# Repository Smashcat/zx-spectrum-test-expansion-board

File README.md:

# zx-spectrum-test-expansion-board

## A test board to plug into the ZX Spectrum expansion port for dev use

This board is used to break out the signals from the expansion header for development use. All signals, except for power, are converted to 3.3V for use with modern microcontrollers. The buttons for WAIT and RESET are optional, but handy for development.

The production folder contains files to submit the board for PCBA production at [JLCPCB](https://jlcpcb.com/) (only the SMD components - as adding thru-hole parts adds 1-2 days to production and costs quite a bit extra - and let's face it, it's pretty simple to solder the headers and buttons!)

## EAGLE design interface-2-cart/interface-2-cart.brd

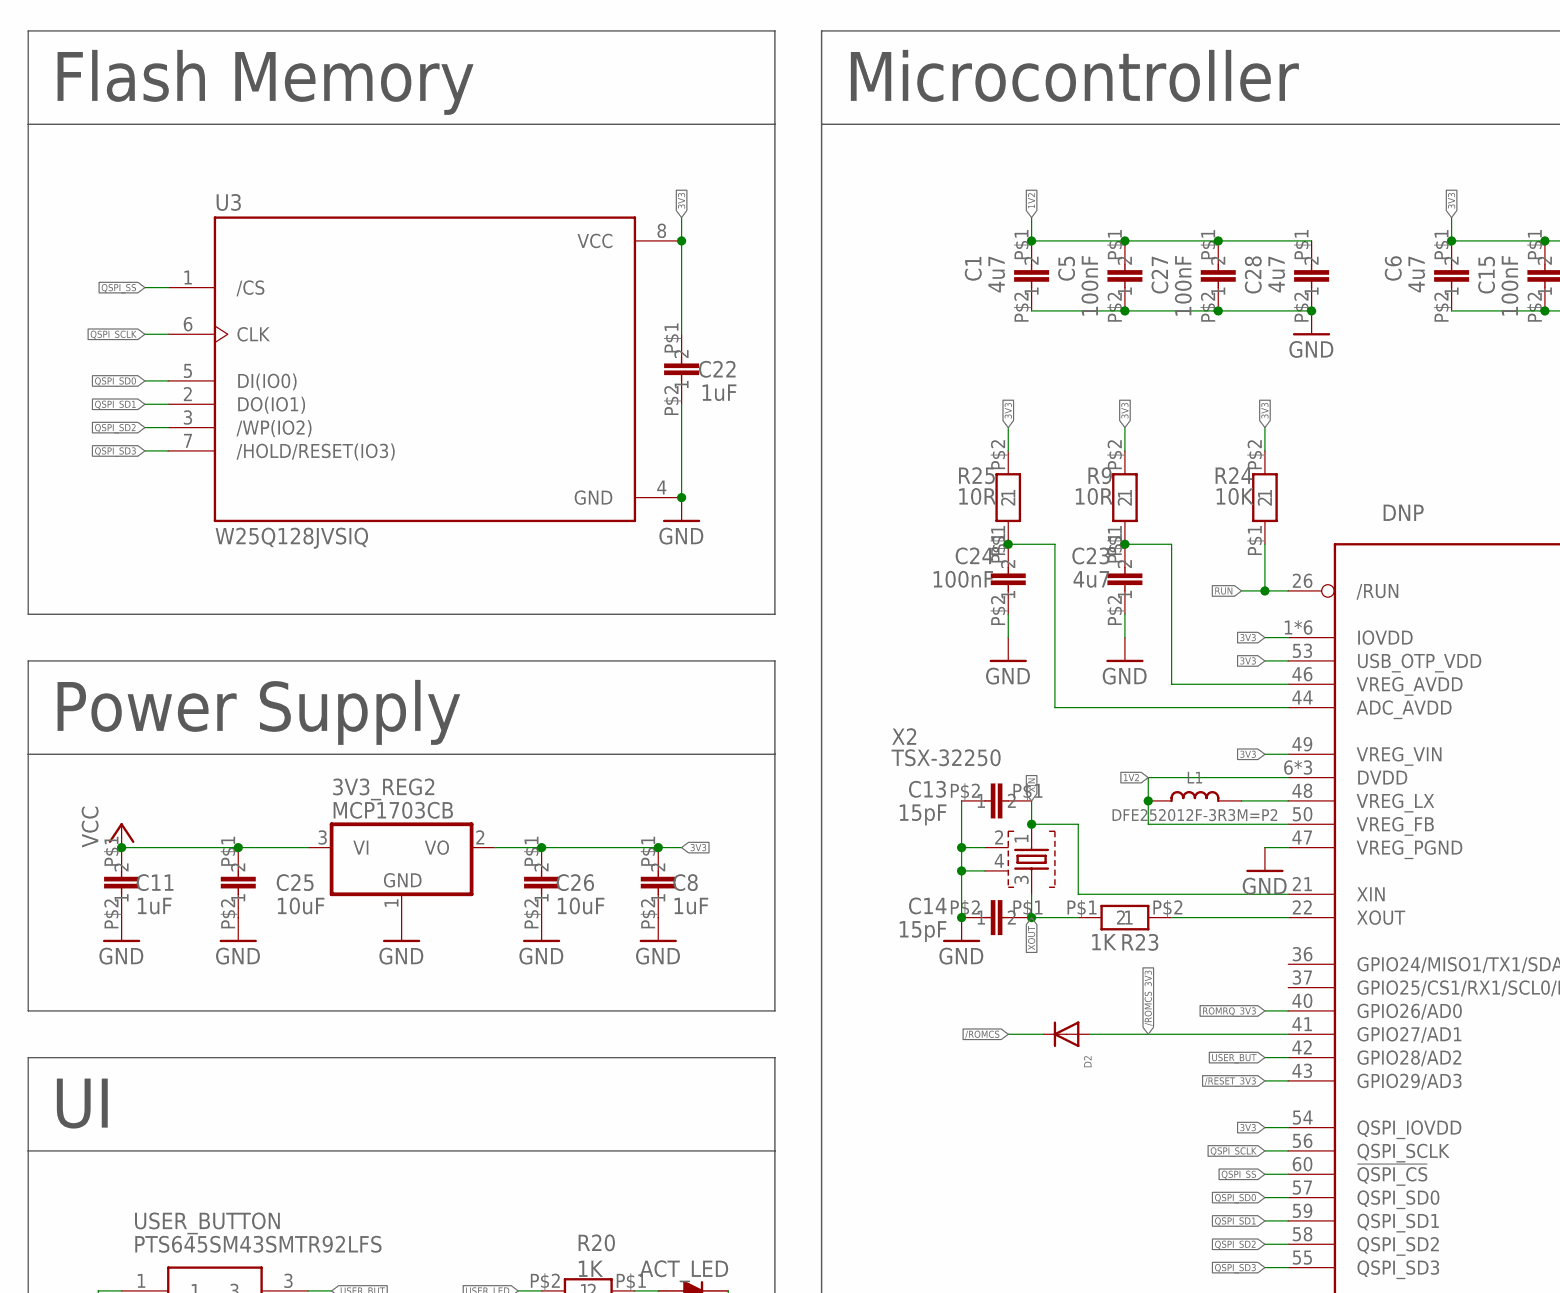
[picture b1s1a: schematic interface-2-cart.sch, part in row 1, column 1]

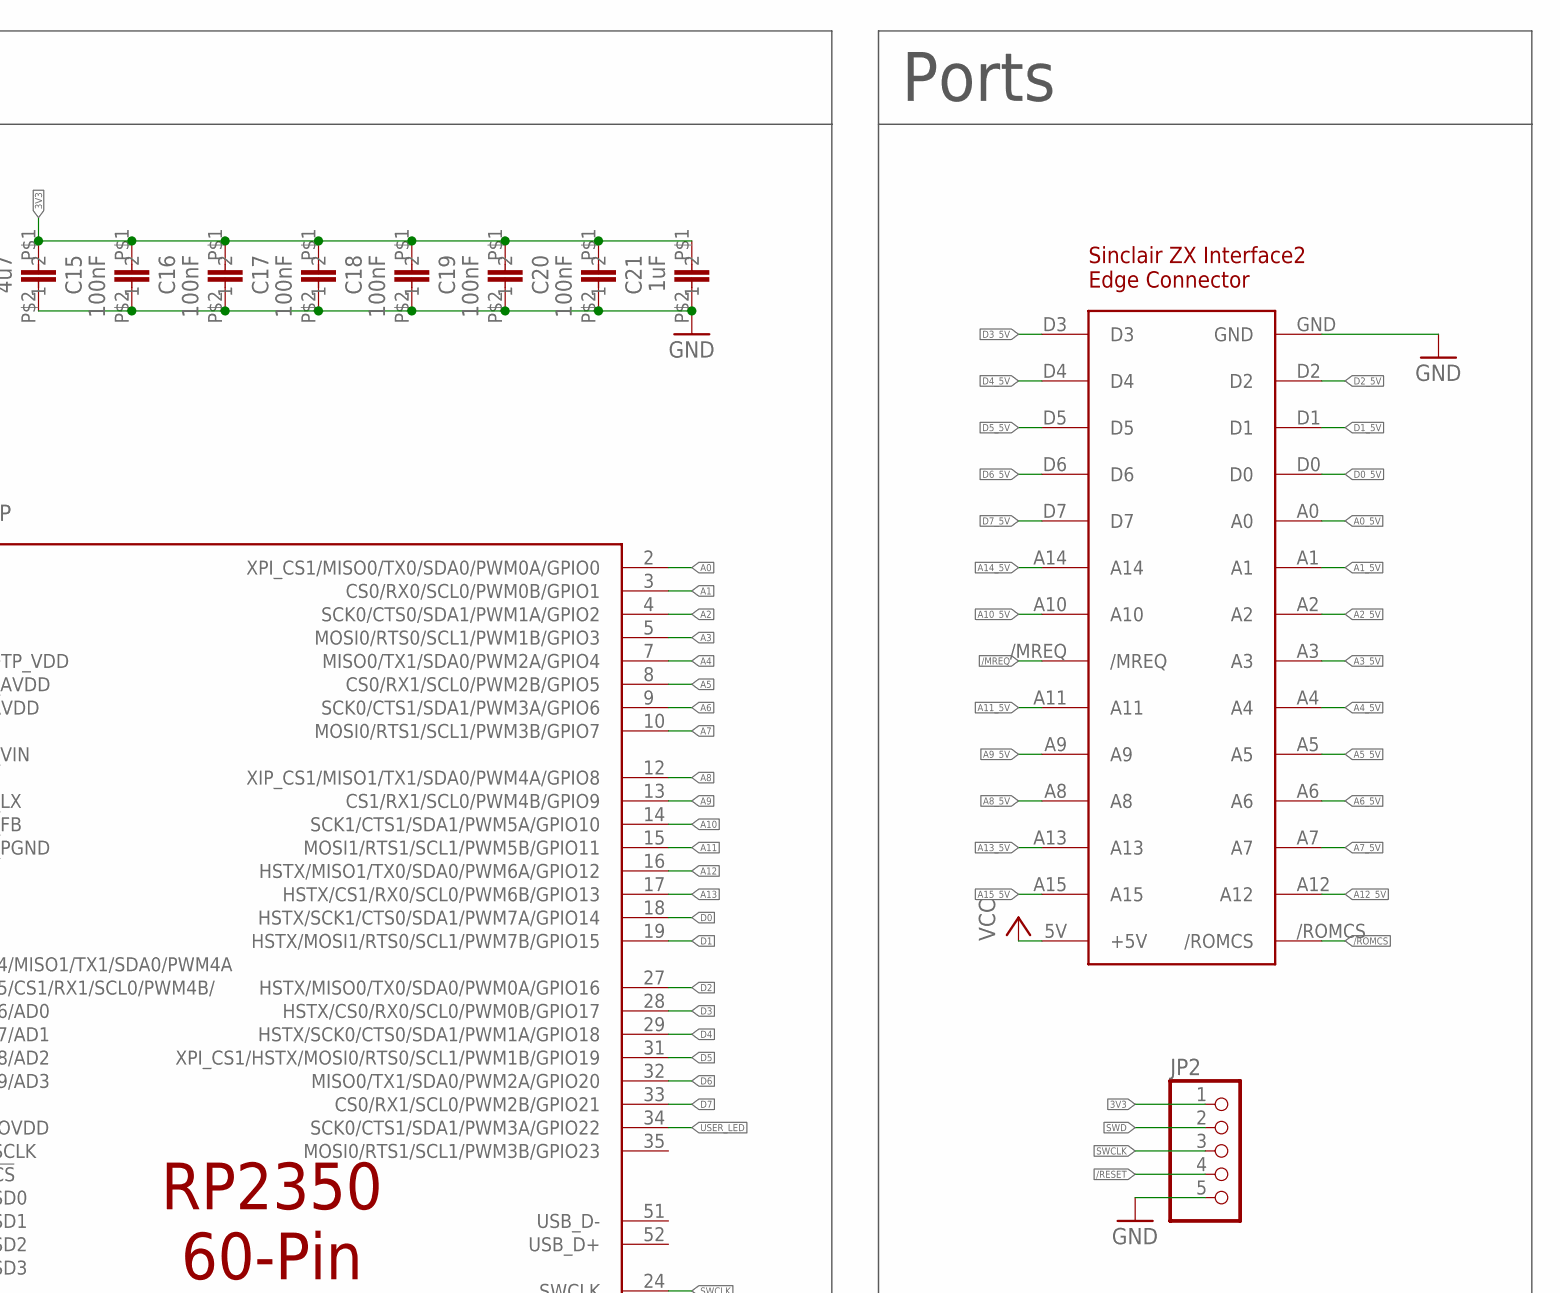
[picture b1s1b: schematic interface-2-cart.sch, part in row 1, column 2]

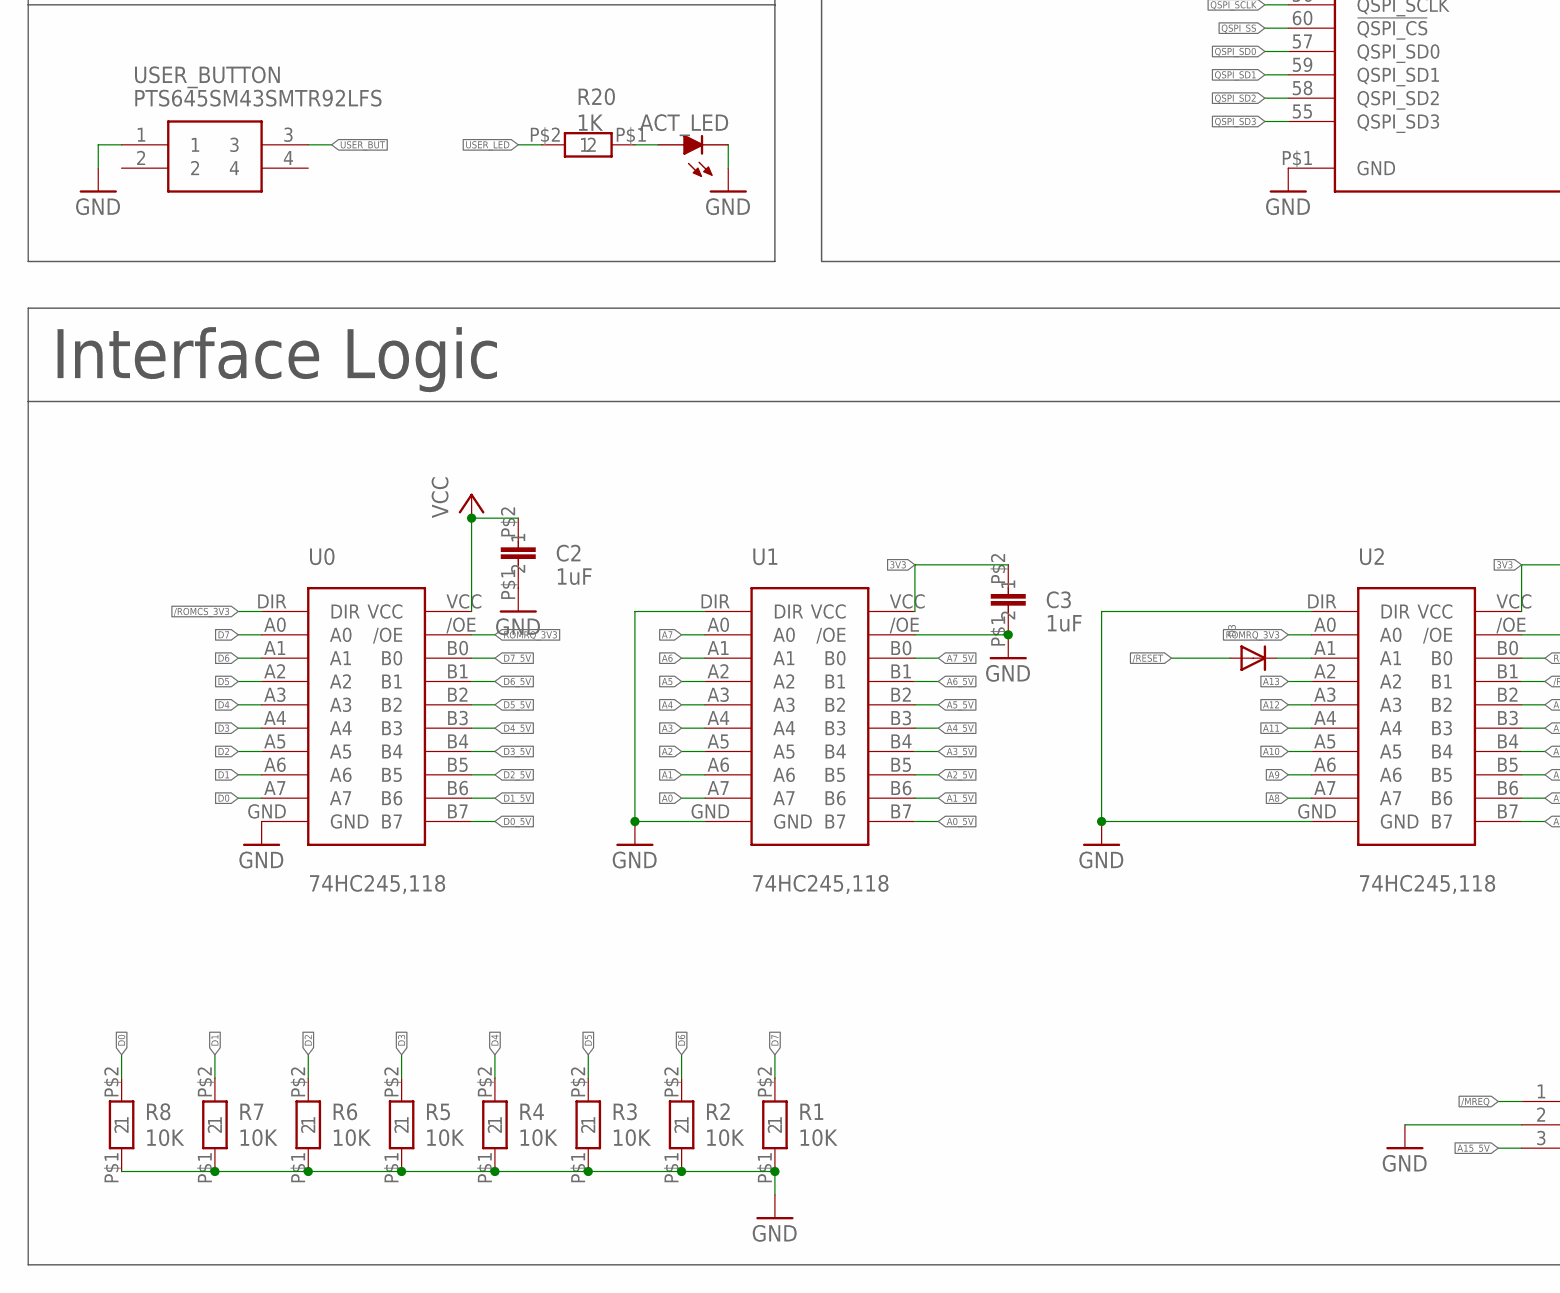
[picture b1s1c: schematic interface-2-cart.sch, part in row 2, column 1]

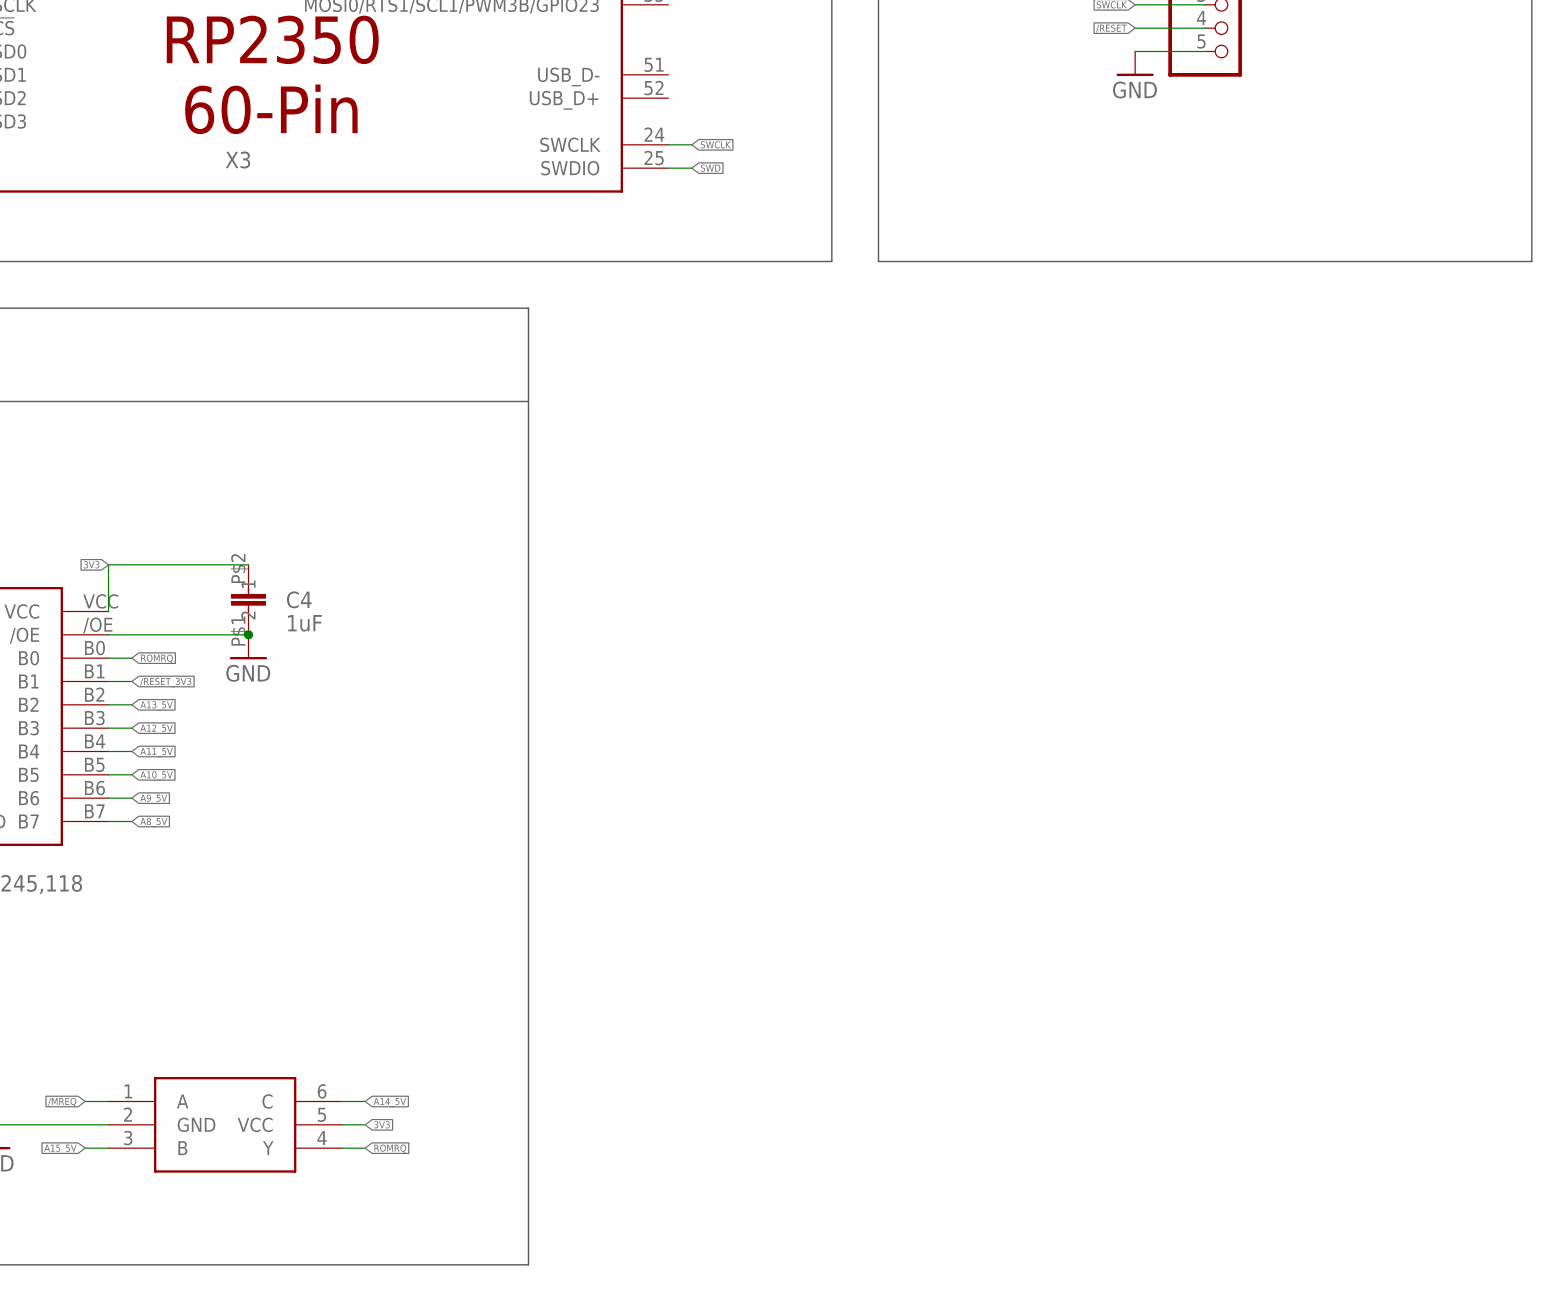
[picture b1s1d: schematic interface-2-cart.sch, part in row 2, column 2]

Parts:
3V3_REG2: MCP1703CB; SOT23
ACT_LED: 20mA; LED_CHIP-LED0603MP
C1, C6, C23, C28: 4u7; C0402
C2, C3, C4, C8, C11, C21, C22: 1uF; C0402
C5, C15, C16, C17, C18, C19, C20, C24, C27: 100nF; C0402
C13, C14: 15pF; C0402
C25, C26: 10uF; C0402
D2, D3: DIODESOD-323F; SOD-323F
JP2: PINHD-1X5; 1X05
L1: DFE252012F-3R3M=P2; INDUCTOR_1007
R1, R2, R3, R4, R5, R6, R7, R8, R24: 10K; 0402
R9, R25: 10R; 0402
R20, R23: 1K; 0402
U0, U1, U2: SOP65P640X110-20N
U3: W25Q128JVSIQ; SOIC127P790X216-8N
U$1: ZX_I2_ROM_EDGE_CONNECTOR; ZX_I2_ROM_EDGE_CONNECTOR_V2
U$2: 74LVC1G332GW,125; SOP65P210X110-6N
USER_BUTTON: PTS645SM43SMTR92LFS; PTS645(SMT)
X2: TSX-32250; TSX-3225
X3: DNP; QFN60_7MM_REDUCEDEPAD

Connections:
1V2: C1.P$1 (1), C5.P$1 (1), C27.P$1 (1), C28.P$1 (1), L1.P$1 (1), X3.6 (DVDD), X3.23 (DVDD), X3.39 (DVDD), X3.50 (VREG_FB)
3V3: 3V3_REG2.2 (VO), C3.P$2 (2), C4.P$2 (2), C6.P$1 (1), C8.P$1 (1), C15.P$1 (1), C16.P$1 (1), C17.P$1 (1), C18.P$1 (1), C19.P$1 (1), C20.P$1 (1), C21.P$1 (1), C22.P$1 (1), C26.P$1 (1), JP2.1, R9.P$2 (2), R24.P$2 (2), R25.P$2 (2), U1.VCC, U2.VCC, U3.8 (VCC), U$2.5 (VCC), X3.1 (IOVDD), X3.11 (IOVDD), X3.20 (IOVDD), X3.30 (IOVDD), X3.38 (IOVDD), X3.45 (IOVDD), X3.49 (VREG_VIN), X3.53 (USB_OTP_VDD), X3.54 (QSPI_IOVDD)
/MREQ: U$1./MREQ, U$2.1 (A)
/RESET: D3.A, JP2.4
/RESET_3V3: U2.B1, X3.43 (GPIO29/AD3)
/ROMCS: D2.C, U$1./ROMCS
/ROMCS_3V3: D2.A, U0.DIR, X3.41 (GPIO27/AD1)
A0: U1.A7, X3.2 (XPI_CS1/MISO0/TX0/SDA0/PWM0A/GPIO0)
A0_5V: U1.B7, U$1.A0
A1: U1.A6, X3.3 (CS0/RX0/SCL0/PWM0B/GPIO1)
A1_5V: U1.B6, U$1.A1
A2: U1.A5, X3.4 (SCK0/CTS0/SDA1/PWM1A/GPIO2)
A2_5V: U1.B5, U$1.A2
A3: U1.A4, X3.5 (MOSI0/RTS0/SCL1/PWM1B/GPIO3)
A3_5V: U1.B4, U$1.A3
A4: U1.A3, X3.7 (MISO0/TX1/SDA0/PWM2A/GPIO4)
A4_5V: U1.B3, U$1.A4
A5: U1.A2, X3.8 (CS0/RX1/SCL0/PWM2B/GPIO5)
A5_5V: U1.B2, U$1.A5
A6: U1.A1, X3.9 (SCK0/CTS1/SDA1/PWM3A/GPIO6)
A6_5V: U1.B1, U$1.A6
A7: U1.A0, X3.10 (MOSI0/RTS1/SCL1/PWM3B/GPIO7)
A7_5V: U1.B0, U$1.A7
A8: U2.A7, X3.12 (XIP_CS1/MISO1/TX1/SDA0/PWM4A/GPIO8)
A8_5V: U2.B7, U$1.A8
A9: U2.A6, X3.13 (CS1/RX1/SCL0/PWM4B/GPIO9)
A9_5V: U2.B6, U$1.A9
A10: U2.A5, X3.14 (SCK1/CTS1/SDA1/PWM5A/GPIO10)
A10_5V: U2.B5, U$1.A10
A11: U2.A4, X3.15 (MOSI1/RTS1/SCL1/PWM5B/GPIO11)
A11_5V: U2.B4, U$1.A11
A12: U2.A3, X3.16 (HSTX/MISO1/TX0/SDA0/PWM6A/GPIO12)
A12_5V: U2.B3, U$1.A12
A13: U2.A2, X3.17 (HSTX/CS1/RX0/SCL0/PWM6B/GPIO13)
A13_5V: U2.B2, U$1.A13
A14_5V: U$1.A14, U$2.6 (C)
A15_5V: U$1.A15, U$2.3 (B)
D0: R8.P$2 (2), U0.A7, X3.18 (HSTX/SCK1/CTS0/SDA1/PWM7A/GPIO14)
D0_5V: U0.B7, U$1.D0
D1: R7.P$2 (2), U0.A6, X3.19 (HSTX/MOSI1/RTS0/SCL1/PWM7B/GPIO15)
D1_5V: U0.B6, U$1.D1
D2: R6.P$2 (2), U0.A5, X3.27 (HSTX/MISO0/TX0/SDA0/PWM0A/GPIO16)
D2_5V: U0.B5, U$1.D2
D3: R5.P$2 (2), U0.A4, X3.28 (HSTX/CS0/RX0/SCL0/PWM0B/GPIO17)
D3_5V: U0.B4, U$1.D3
D4: R4.P$2 (2), U0.A3, X3.29 (HSTX/SCK0/CTS0/SDA1/PWM1A/GPIO18)
D4_5V: U0.B3, U$1.D4
D5: R3.P$2 (2), U0.A2, X3.31 (XPI_CS1/HSTX/MOSI0/RTS0/SCL1/PWM1B/GPIO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)
D5_5V: U0.B2, U$1.D5
D6: R2.P$2 (2), U0.A1, X3.32 (MISO0/TX1/SDA0/PWM2A/GPIO20)
D6_5V: U0.B1, U$1.D6
D7: R1.P$2 (2), U0.A0, X3.33 (CS0/RX1/SCL0/PWM2B/GPIO21)
D7_5V: U0.B0, U$1.D7
GND: 3V3_REG2.1 (GND), ACT_LED.C, C1.P$2 (2), C2.P$1 (1), C3.P$1 (1), C4.P$1 (1), C5.P$2 (2), C6.P$2 (2), C8.P$2 (2), C11.P$2 (2), C13.P$2 (2), C14.P$2 (2), C15.P$2 (2), C16.P$2 (2), C17.P$2 (2), C18.P$2 (2), C19.P$2 (2), C20.P$2 (2), C21.P$2 (2), C22.P$2 (2), C23.P$2 (2), C24.P$2 (2), C25.P$2 (2), C26.P$2 (2), C27.P$2 (2), C28.P$2 (2), JP2.5, R1.P$1 (1), R2.P$1 (1), R3.P$1 (1), R4.P$1 (1), R5.P$1 (1), R6.P$1 (1), R7.P$1 (1), R8.P$1 (1), U0.GND, U1./OE, U1.DIR, U1.GND, U2./OE, U2.DIR, U2.GND, U3.4 (GND), U$1.GND, U$2.2 (GND), USER_BUTTON.1, X2.2, X2.4, X3.47 (VREG_PGND), X3.P$1 (GND)
unnamed: ACT_LED.A, R20.P$1 (1)
unnamed: D3.C, U2.A1
unnamed: R23.P$2 (2), X3.22 (XOUT)
unnamed: L1.P$2 (2), X3.48 (VREG_LX)
unnamed: C23.P$1 (1), R9.P$1 (1), X3.46 (VREG_AVDD)
unnamed: C24.P$1 (1), R25.P$1 (1), X3.44 (ADC_AVDD)
QSPI_SCLK: U3.6 (CLK), X3.56 (QSPI_SCLK)
QSPI_SD0: U3.5 (DI(IO0)), X3.57 (QSPI_SD0)
QSPI_SD1: U3.2 (DO(IO1)), X3.59 (QSPI_SD1)
QSPI_SD2: U3.3 (/WP(IO2)), X3.58 (QSPI_SD2)
QSPI_SD3: U3.7 (/HOLD/RESET(IO3)), X3.55 (QSPI_SD3)
QSPI_SS: U3.1 (/CS), X3.60 (!QSPI_CS)
ROMRQ: U2.B0, U$2.4 (Y)
ROMRQ_3V3: U0./OE, U2.A0, X3.40 (GPIO26/AD0)
RUN: R24.P$1 (1), X3.26 (/RUN)
SWCLK: JP2.3, X3.24 (SWCLK)
SWD: JP2.2, X3.25 (SWDIO)
USER_BUT: USER_BUTTON.3, X3.42 (GPIO28/AD2)
USER_LED: R20.P$2 (2), X3.34 (SCK0/CTS1/SDA1/PWM3A/GPIO22)
VCC: 3V3_REG2.3 (VI), C2.P$2 (2), C11.P$1 (1), C25.P$1 (1), U0.VCC, U$1.5V (+5V)
XIN: C13.P$1 (1), X2.1, X3.21 (XIN)
XOUT: C14.P$1 (1), R23.P$1 (1), X2.3

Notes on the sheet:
Microcontroller
Ports
Flash Memory
Power Supply
Interface Logic

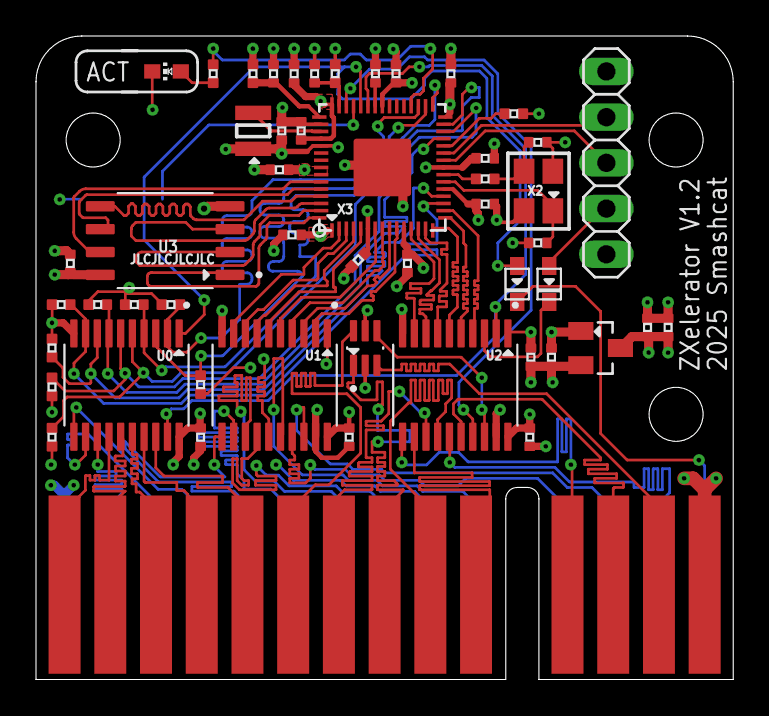
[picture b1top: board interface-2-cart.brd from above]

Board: 4 copper layers, 38.7 x 35.8 mm, 52 parts (1 on the bottom side), 76 nets.

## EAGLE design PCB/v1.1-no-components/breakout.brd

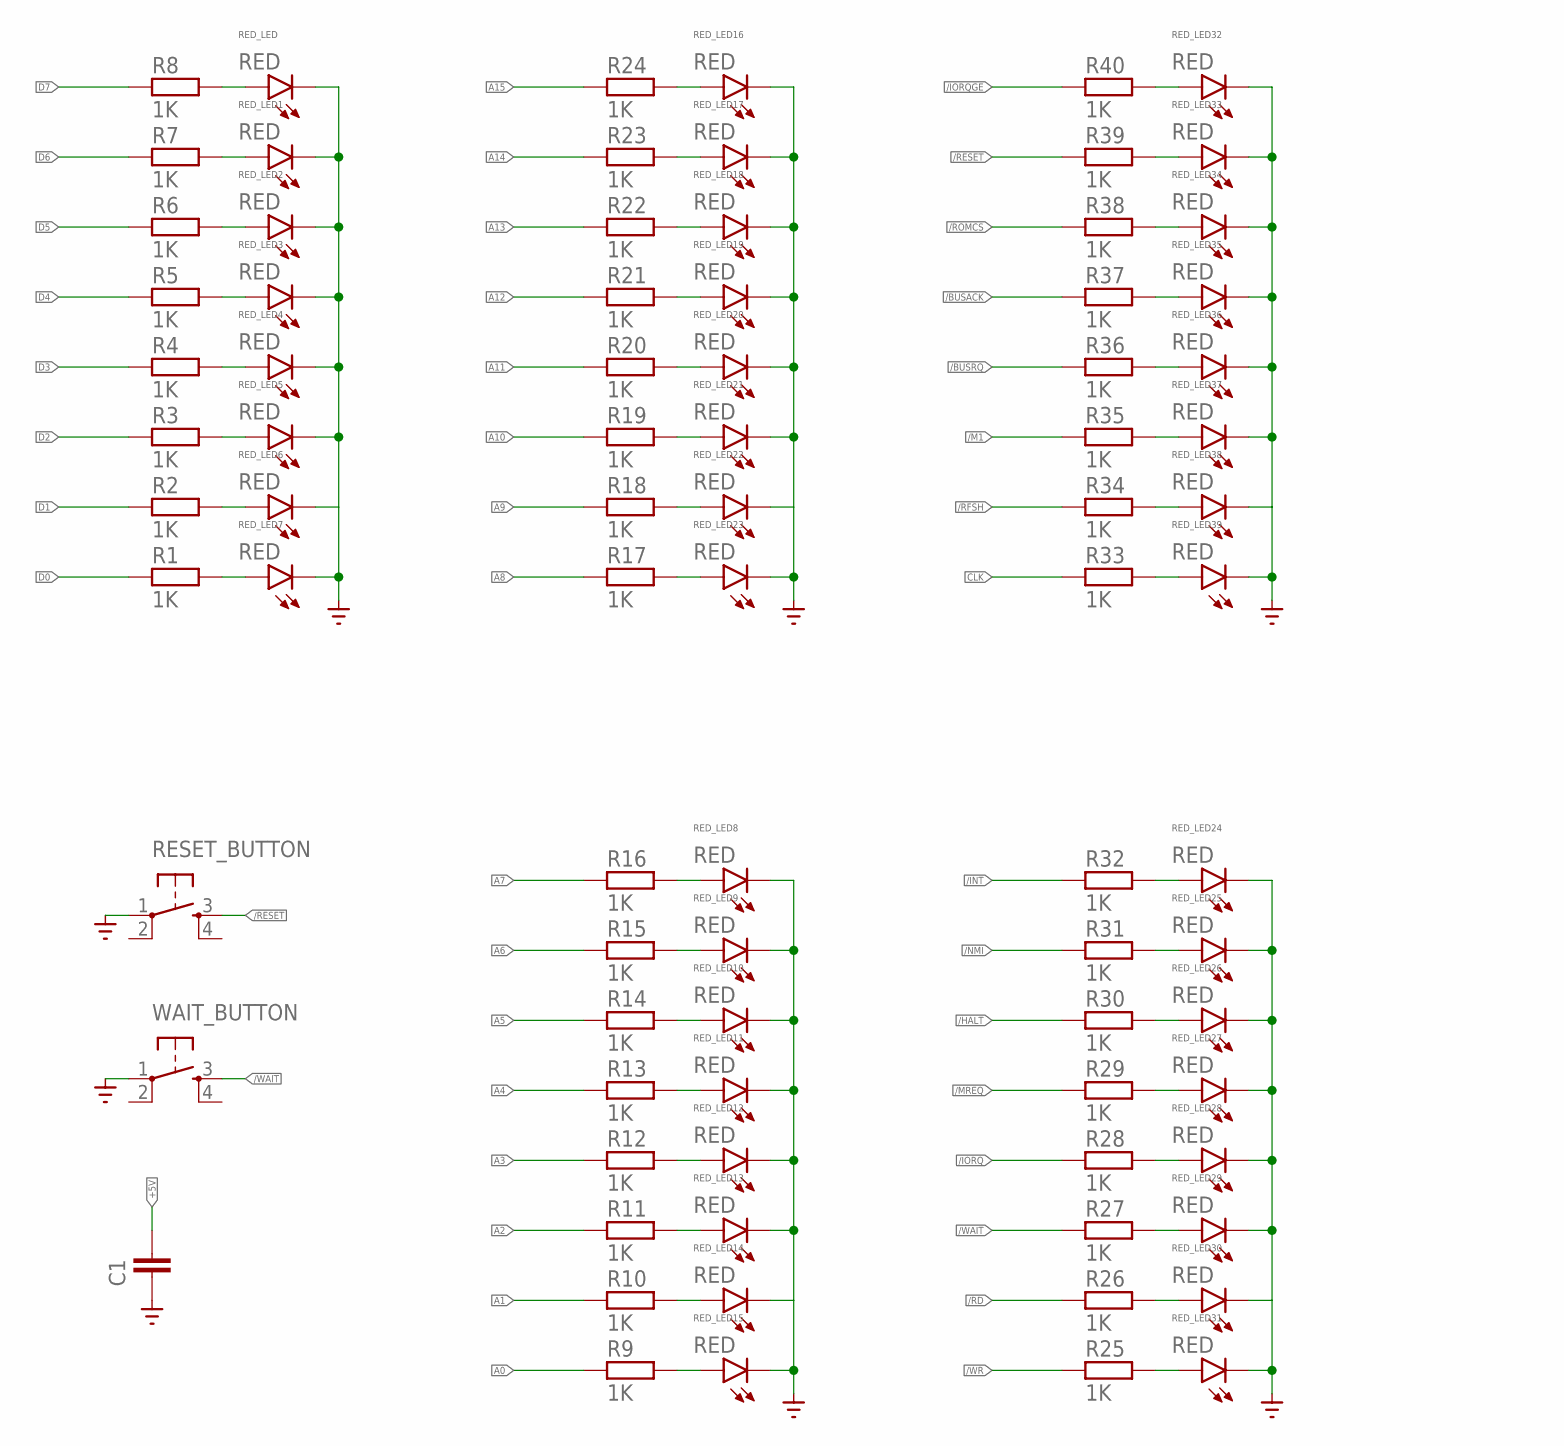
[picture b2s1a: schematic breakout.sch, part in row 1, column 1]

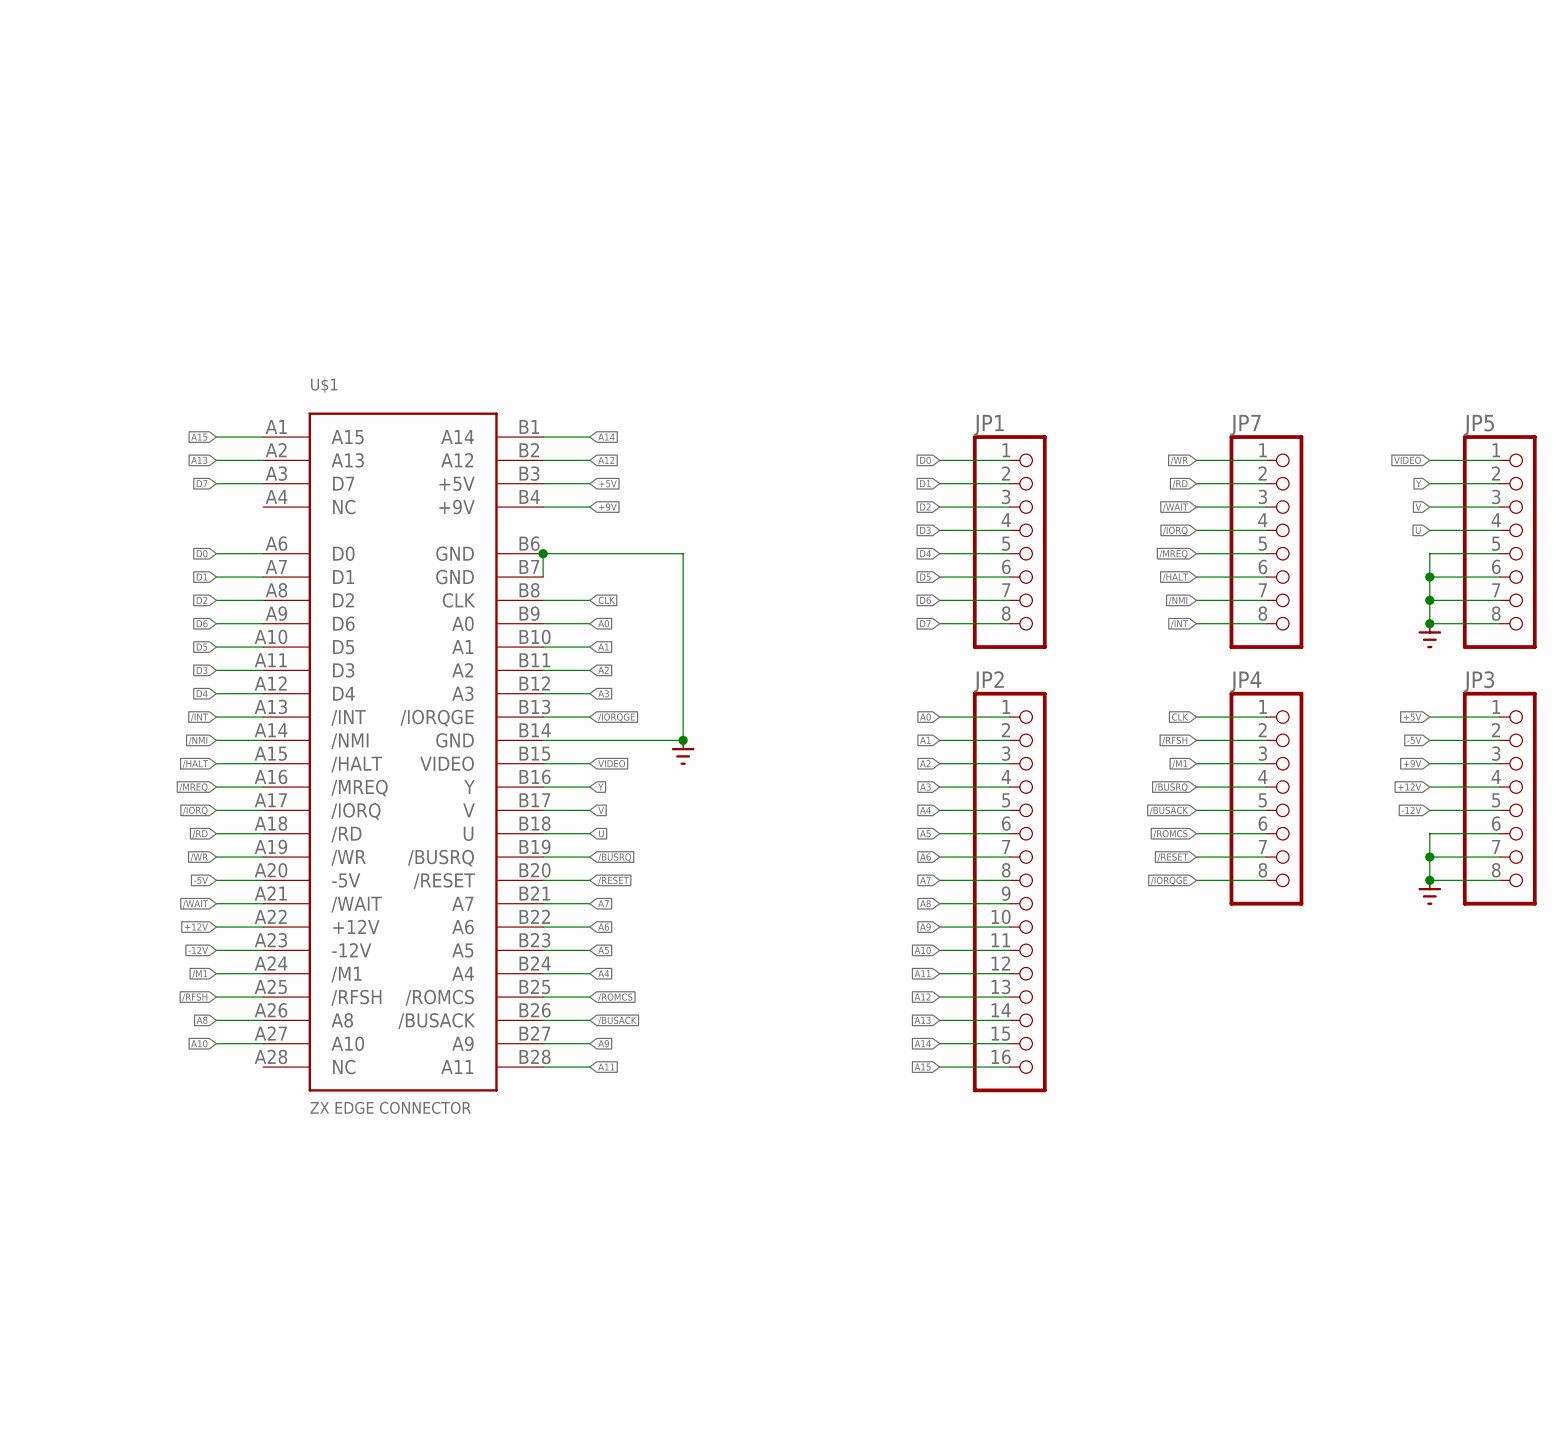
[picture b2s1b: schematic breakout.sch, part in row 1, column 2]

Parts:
C1: 1u; C0402
JP1, JP3, JP4, JP5, JP7: PINHD-1X8; 1X08
JP2: PINHD-1X16; 1X16
R1, R2, R3, R4, R5, R6, R7, R8, R9, R10, R11, R12, R13, R14, R15, R16, R17, R18, R19, R20, R21, R22, R23, R24, R25, R26, R27, R28, R29, R30, R31, R32, R33, R34, R35, R36, R37, R38, R39, R40: 1K; R0402
RED_LED, RED_LED1, RED_LED2, RED_LED3, RED_LED4, RED_LED5, RED_LED6, RED_LED7, RED_LED8, RED_LED9, RED_LED10, RED_LED11, RED_LED12, RED_LED13, RED_LED14, RED_LED15, RED_LED16, RED_LED17, RED_LED18, RED_LED19, RED_LED20, RED_LED21, RED_LED22, RED_LED23, RED_LED24, RED_LED25, RED_LED26, RED_LED27, RED_LED28, RED_LED29, RED_LED30, RED_LED31, RED_LED32, RED_LED33, RED_LED34, RED_LED35, RED_LED36, RED_LED37, RED_LED38, RED_LED39: RED; CHIPLED_0603
RESET_BUTTON: 10-XX; B3F-10XX-3D
U$1: ZX-SPECTRUM-EDGE-CONNECTOR
WAIT_BUTTON: 10-XX; B3F-10XX-3D

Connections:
+5V: C1.1, JP3.1, U$1.B3 (+5V)
+9V: JP3.3, U$1.B4 (+9V)
+12V: JP3.4, U$1.A22 (+12V)
-5V: JP3.2, U$1.A20 (-5V)
-12V: JP3.5, U$1.A23 (-12V)
/BUSACK: JP4.5, R37.1, U$1.B26 (/BUSACK)
/BUSRQ: JP4.4, R36.1, U$1.B19 (/BUSRQ)
/HALT: JP7.6, R30.1, U$1.A15 (/HALT)
/INT: JP7.8, R32.1, U$1.A13 (/INT)
/IORQ: JP7.4, R28.1, U$1.A17 (/IORQ)
/IORQGE: JP4.8, R40.1, U$1.B13 (/IORQGE)
/M1: JP4.3, R35.1, U$1.A24 (/M1)
/MREQ: JP7.5, R29.1, U$1.A16 (/MREQ)
/NMI: JP7.7, R31.1, U$1.A14 (/NMI)
/RD: JP7.2, R26.1, U$1.A18 (/RD)
/RESET: JP4.7, R39.1, RESET_BUTTON.3 (S), U$1.B20 (/RESET)
/RFSH: JP4.2, R34.1, U$1.A25 (/RFSH)
/ROMCS: JP4.6, R38.1, U$1.B25 (/ROMCS)
/WAIT: JP7.3, R27.1, U$1.A21 (/WAIT), WAIT_BUTTON.3 (S)
/WR: JP7.1, R25.1, U$1.A19 (/WR)
A0: JP2.1, R9.1, U$1.B9 (A0)
A1: JP2.2, R10.1, U$1.B10 (A1)
A2: JP2.3, R11.1, U$1.B11 (A2)
A3: JP2.4, R12.1, U$1.B12 (A3)
A4: JP2.5, R13.1, U$1.B24 (A4)
A5: JP2.6, R14.1, U$1.B23 (A5)
A6: JP2.7, R15.1, U$1.B22 (A6)
A7: JP2.8, R16.1, U$1.B21 (A7)
A8: JP2.9, R17.1, U$1.A26 (A8)
A9: JP2.10, R18.1, U$1.B27 (A9)
A10: JP2.11, R19.1, U$1.A27 (A10)
A11: JP2.12, R20.1, U$1.B28 (A11)
A12: JP2.13, R21.1, U$1.B2 (A12)
A13: JP2.14, R22.1, U$1.A2 (A13)
A14: JP2.15, R23.1, U$1.B1 (A14)
A15: JP2.16, R24.1, U$1.A1 (A15)
CLK: JP4.1, R33.1, U$1.B8 (CLK)
D0: JP1.1, R1.1, U$1.A6 (D0)
D1: JP1.2, R2.1, U$1.A7 (D1)
D2: JP1.3, R3.1, U$1.A8 (D2)
D3: JP1.4, R4.1, U$1.A11 (D3)
D4: JP1.5, R5.1, U$1.A12 (D4)
D5: JP1.6, R6.1, U$1.A10 (D5)
D6: JP1.7, R7.1, U$1.A9 (D6)
D7: JP1.8, R8.1, U$1.A3 (D7)
GND: C1.2, JP3.6, JP3.7, JP3.8, JP5.5, JP5.6, JP5.7, JP5.8, RED_LED.C, RED_LED1.C, RED_LED2.C, RED_LED3.C, RED_LED4.C, RED_LED5.C, RED_LED6.C, RED_LED7.C, RED_LED8.C, RED_LED9.C, RED_LED10.C, RED_LED11.C, RED_LED12.C, RED_LED13.C, RED_LED14.C, RED_LED15.C, RED_LED16.C, RED_LED17.C, RED_LED18.C, RED_LED19.C, RED_LED20.C, RED_LED21.C, RED_LED22.C, RED_LED23.C, RED_LED24.C, RED_LED25.C, RED_LED26.C, RED_LED27.C, RED_LED28.C, RED_LED29.C, RED_LED30.C, RED_LED31.C, RED_LED32.C, RED_LED33.C, RED_LED34.C, RED_LED35.C, RED_LED36.C, RED_LED37.C, RED_LED38.C, RED_LED39.C, RESET_BUTTON.1, U$1.B6 (GND), U$1.B7 (GND), U$1.B14 (GND), WAIT_BUTTON.1
unnamed: R8.2, RED_LED.A
unnamed: R7.2, RED_LED1.A
unnamed: R6.2, RED_LED2.A
unnamed: R5.2, RED_LED3.A
unnamed: R4.2, RED_LED4.A
unnamed: R3.2, RED_LED5.A
unnamed: R2.2, RED_LED6.A
unnamed: R1.2, RED_LED7.A
unnamed: R16.2, RED_LED8.A
unnamed: R15.2, RED_LED9.A
unnamed: R14.2, RED_LED10.A
unnamed: R13.2, RED_LED11.A
unnamed: R12.2, RED_LED12.A
unnamed: R11.2, RED_LED13.A
unnamed: R10.2, RED_LED14.A
unnamed: R9.2, RED_LED15.A
unnamed: R24.2, RED_LED16.A
unnamed: R23.2, RED_LED17.A
unnamed: R22.2, RED_LED18.A
unnamed: R21.2, RED_LED19.A
unnamed: R20.2, RED_LED20.A
unnamed: R19.2, RED_LED21.A
unnamed: R18.2, RED_LED22.A
unnamed: R17.2, RED_LED23.A
unnamed: R32.2, RED_LED24.A
unnamed: R31.2, RED_LED25.A
unnamed: R30.2, RED_LED26.A
unnamed: R29.2, RED_LED27.A
unnamed: R28.2, RED_LED28.A
unnamed: R27.2, RED_LED29.A
unnamed: R26.2, RED_LED30.A
unnamed: R25.2, RED_LED31.A
unnamed: R40.2, RED_LED32.A
unnamed: R39.2, RED_LED33.A
unnamed: R38.2, RED_LED34.A
unnamed: R37.2, RED_LED35.A
unnamed: R36.2, RED_LED36.A
unnamed: R35.2, RED_LED37.A
unnamed: R34.2, RED_LED38.A
unnamed: R33.2, RED_LED39.A
U: JP5.4, U$1.B18 (U)
V: JP5.3, U$1.B17 (V)
VIDEO: JP5.1, U$1.B15 (VIDEO)
Y: JP5.2, U$1.B16 (Y)

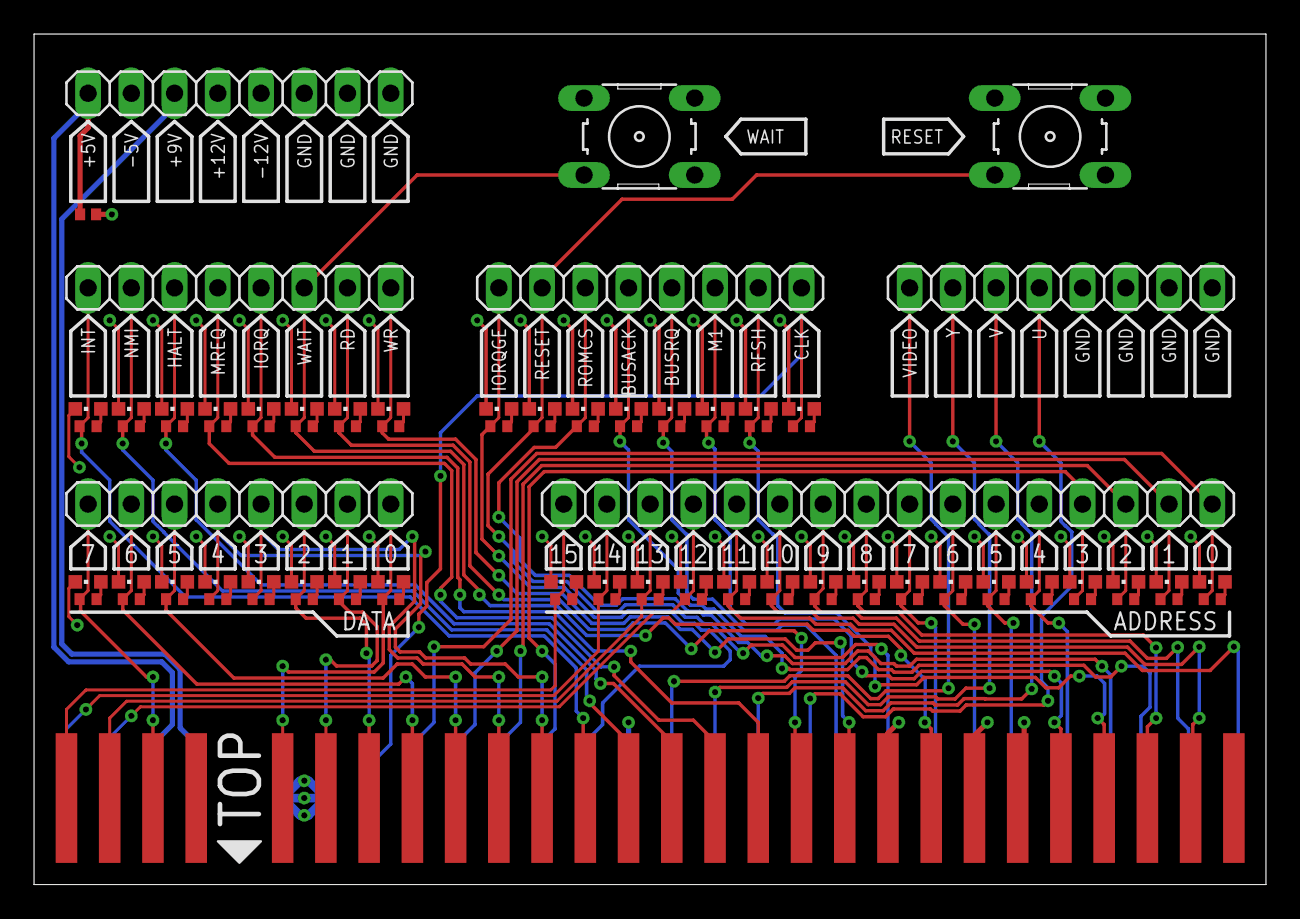
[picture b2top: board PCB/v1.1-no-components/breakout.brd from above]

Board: 4 copper layers, 72.4 x 50.0 mm, 90 parts (0 on the bottom side), 90 nets.

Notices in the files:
parts and their libraries:
microbuilder: This work is placed in the public domain, and may be freely used for commercial and non-commercial work with the following conditions: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
